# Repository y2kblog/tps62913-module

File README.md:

# TPS62913 低ノイズ・低リップル 可変出力降圧モジュール

## 概要

低ノイズ・低リップルの降圧型DC/DCコンバータ TPS62913 (Texas Instruments Inc.製) を搭載したモジュールです。  
低ノイズLDOに匹敵する**20µV<sub>RMS</sub>の1/fノイズ**と、IC内蔵のフェライトビーズLCフィルタ補償機能による**10µV<sub>RMS</sub>未満の低リップル**を実現しており、ノイズの影響を受けやすいアプリケーション（例：実験用精密電源、高速ADC、レーダー）の電源供給に適しています。  
また、スイッチングレギュレータのため最大3.0Aの電流を出力できます。  

### 仕様
- 入力電圧：3.0～17.0V
- 出力電圧：0.9～5.1V (基板上の半固定抵抗で調整)
- 最大出力電流：3.0A
- 1/fノイズ：20µV<sub>RMS</sub> (100Hz～100kHz)
- 電圧リップル：10µV<sub>RMS</sub>未満 (typ.)
- イネーブルピン付き
- パワー・グッドピン付き
- 出力放電機能：有効
- ソフトスタート時間：10.7ms (typ.)
- 基板サイズ：20mm × 22mm
- ピン間隔：2.54mm
<!--
- スイッチング周波数：2.2MHz (typ.)
- スペクトラム拡散変調：有効
-->

## 販売  
[スイッチサイエンス委託販売ページ](https://www.switch-science.com/catalog/7619/)  
※大量注文や在庫に関する問い合わせは[こちら](mailto:info.y2kb@gmail.com)までご連絡ください。  

## ピンアサイン
<table>
    <thead>
        <tr>
            <th>#</th>
            <th>ピン名</th>
            <th>表面シルク</th>
            <th>説明</th>
        </tr>
    </thead>
    <tbody>
        <tr>
            <td>1</td>
            <td>VIN</td>
            <td>I</td>
            <td>電源入力</td>
        </tr>
        <tr>
            <td>2</td>
            <td>GND</td>
            <td>G</td>
            <td>グラウンド（基準電位）</td>
        </tr>
        <tr>
            <td>3</td>
            <td>VOUT</td>
            <td>O</td>
            <td>電源出力</td>
        </tr>
        <tr>
            <td>4</td>
            <td>EN</td>
            <td>E</td>
            <td>イネーブル<br>デフォルトではENピンはVINピンに基板内部で接続されており、常時出力ONです。基板裏面のJP1ショートジャンパをカッター等で切断するとENピンによる出力ON/OFF制御が可能になり、ENピンに約1V以上を印加すると出力がONになります。</td>
        </tr>
        <tr>
            <td>5</td>
            <td>PG</td>
            <td>P</td>
            <td>パワー・グッド<br>VOUTがパワー・グッド閾値電圧を下回るとGNDと同等の電圧となります。出力電圧が良好な場合はVOUTと同等の電圧となります。</td>
        </tr>
    </tbody>
</table>

## 回路図  

<!--<a href="/hardware/tps62913-module.pdf">回路図(PDF)</a>  -->

## 基板寸法

## 資料
- 2Dデータ(DXF)：<a href="https://github.com/y2kblog/tps62913-module/raw/master/hardware/dxf/tps62913-module_dxf.zip" download="">tps62913-module_dxf.zip</a>  
- 3Dデータ(STEP)：<a href="https://github.com/y2kblog/tps62913-module/raw/master/hardware/step/tps62913-module_step.zip" download="">tps62913-module_step.zip</a>  
- [TPS61099xデータシート](https://www.tij.co.jp/lit/gpn/tps62913)

## License
MIT License, see `/LICENSE`.

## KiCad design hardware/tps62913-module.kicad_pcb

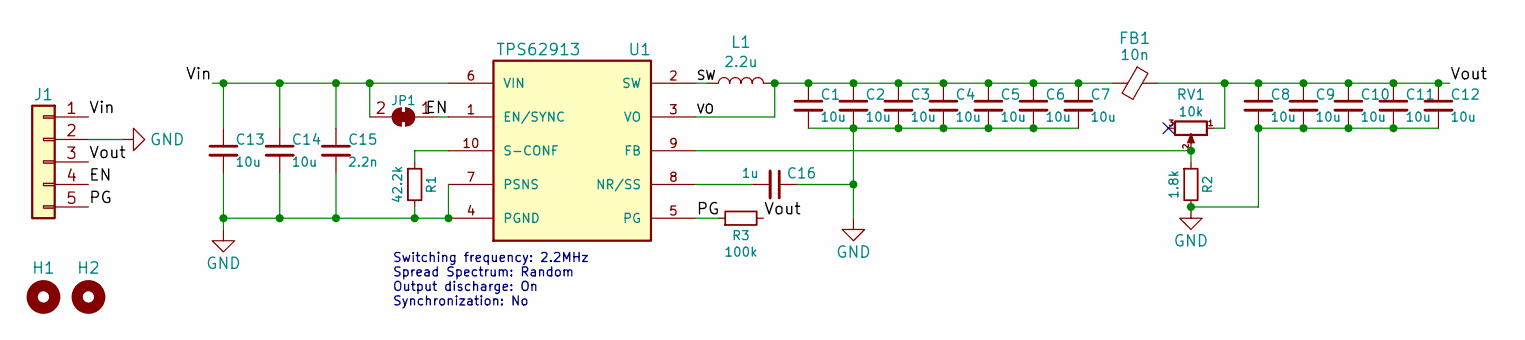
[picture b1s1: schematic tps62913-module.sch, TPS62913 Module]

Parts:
C1, C2, C3, C4, C5, C6, C7, C8, C9, C10, C11, C12: 10u; C_0603; Rating >=10V
C13, C14: 10u; C_0805
C15: 2.2n; C_0402; Rating >=25V
C16: 1u; C_0402
FB1: 10n; C_0603
H1, H2: MountingHole; MountingHole_3.2mm_M3
J1: Conn_01x05; SIL-5
JP1: SolderJumper_2_Bridged; SolderJumper-2_P1.3mm_Bridged_RoundedPad1.0x1.5mm
L1: 2.2u; SWPA-2020
R1: 42.2k; R_0603
R2: 1.8k; R_0603
R3: 100k; R_0603
RV1: 10k; VR_3362P-1
U1: TPS62913; TPS6291x; Digikey # 296-TPS62913RPURCT-ND

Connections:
/EN: J1.4, JP1.1 (A), U1.1 (EN/SYNC)
/PG: J1.5, R3.1, U1.5 (PG)
/SW: L1.1, U1.2 (SW)
/VO: C1.1, C2.1, C3.1, C4.1, C5.1, C6.1, C7.1, FB1.2, L1.2, U1.3 (VO)
/Vin: C13.1, C14.1, C15.1, J1.1, JP1.2 (B), U1.6 (VIN)
/Vout: C8.1, C9.1, C10.1, C11.1, C12.1, FB1.1, J1.3, R3.2, RV1.1
GND: C1.2, C2.2, C3.2, C4.2, C5.2, C6.2, C7.2, C8.2, C9.2, C10.2, C11.2, C12.2, C13.2, C14.2, C15.2, C16.1, J1.2, R1.2, R2.2, U1.4 (PGND), U1.7 (PSNS)
unnamed: C16.2, U1.8 (NR/SS)
unnamed: R1.1, U1.10 (S-CONF)
unnamed: R2.1, RV1.2, U1.9 (FB)

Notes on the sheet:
Switching frequency: 2.2MHz Spread Spectrum: Random Output discharge: On Synchronization: No

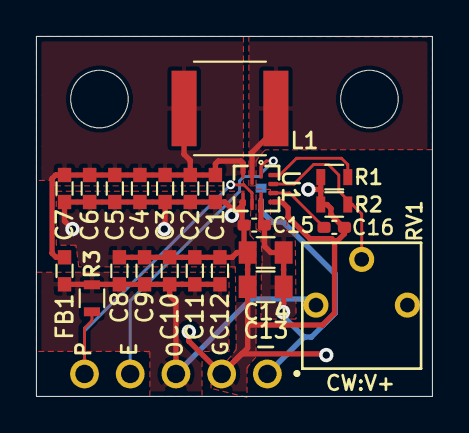
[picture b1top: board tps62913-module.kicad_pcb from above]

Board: 2 copper layers, 22.0 x 20.0 mm, 27 parts (1 on the bottom side), 10 nets.

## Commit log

2021-09-11 add gitignore
2021-11-08 add README and images
2021-11-30 add link
